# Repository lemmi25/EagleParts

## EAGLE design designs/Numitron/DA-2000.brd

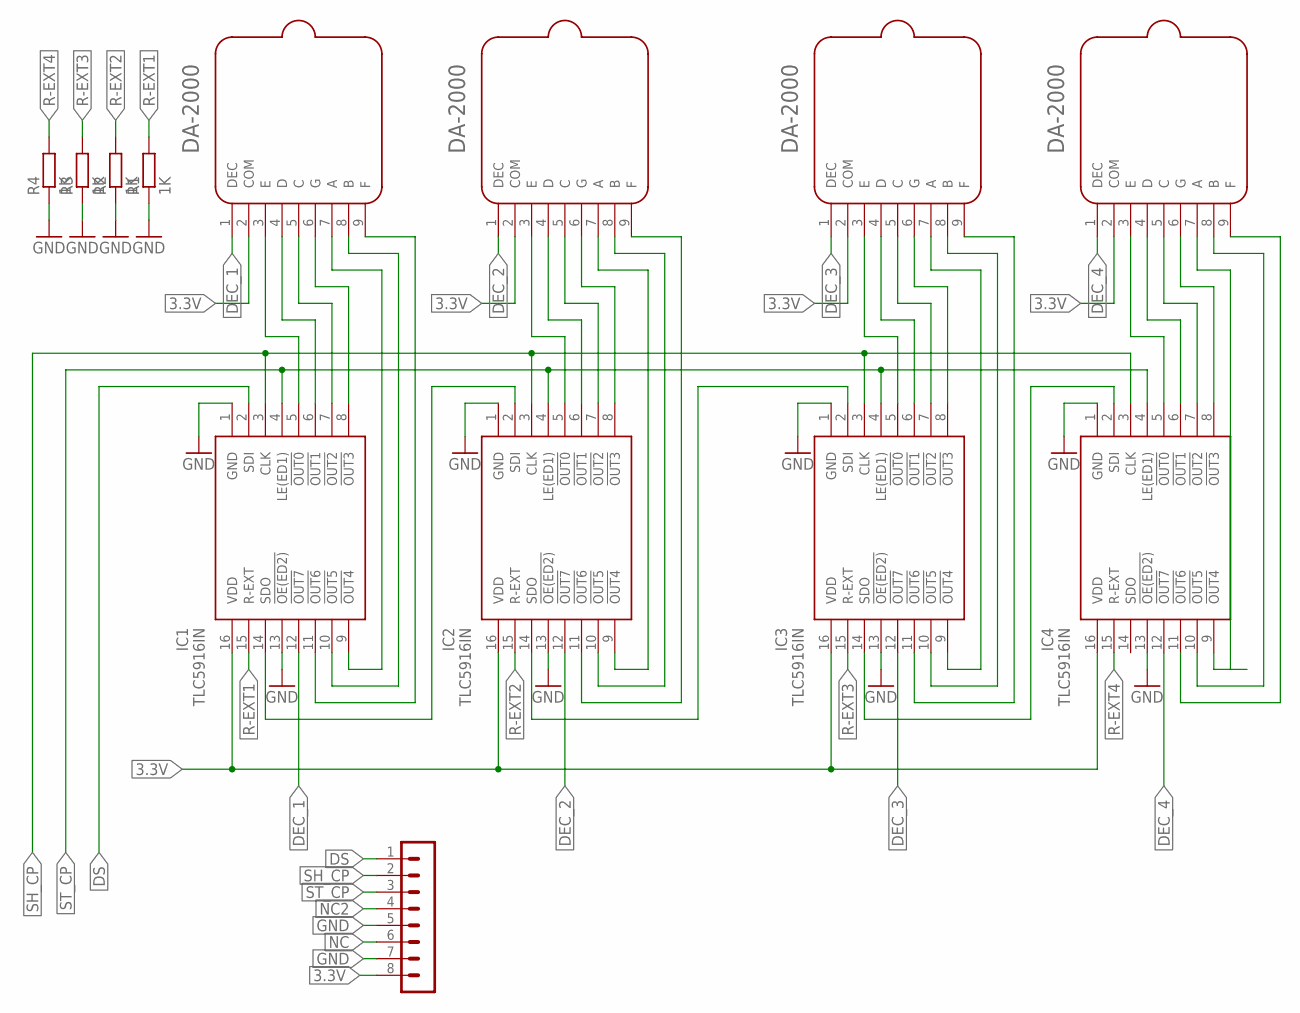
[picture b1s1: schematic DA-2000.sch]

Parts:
IC1, IC2, IC3, IC4: TLC5916IN; DIP794W53P254L1930H508Q16N
R1, R2, R3, R4: 1K; R1206
SV2: PINHEADER-1X8; MA08-1
U$1, U$2, U$3, U$4: DA-2000

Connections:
3.3V: IC1.16 (VDD), IC2.16 (VDD), IC3.16 (VDD), IC4.16 (VDD), SV2.8, U$1.2 (COM), U$2.2 (COM), U$3.2 (COM), U$4.2 (COM)
DEC_1: IC1.12 (!OUT7), U$1.1 (DEC)
DEC_2: IC2.12 (!OUT7), U$2.1 (DEC)
DEC_3: IC3.12 (!OUT7), U$3.1 (DEC)
DEC_4: IC4.12 (!OUT7), U$4.1 (DEC)
DS: IC1.2 (SDI), SV2.1
GND: IC1.1 (GND), IC1.13 (!OE(ED2)), IC2.1 (GND), IC2.13 (!OE(ED2)), IC3.1 (GND), IC3.13 (!OE(ED2)), IC4.1 (GND), IC4.13 (!OE(ED2)), R1.1, R2.1, R3.1, R4.1, SV2.5, SV2.7
unnamed: IC3.8 (!OUT3), U$3.6 (G)
unnamed: IC3.9 (!OUT4), U$3.7 (A)
unnamed: IC1.5 (!OUT0), U$1.3 (E)
unnamed: IC1.6 (!OUT1), U$1.4 (D)
unnamed: IC1.7 (!OUT2), U$1.5 (C)
unnamed: IC1.8 (!OUT3), U$1.6 (G)
unnamed: IC4.8 (!OUT3), U$4.6 (G)
unnamed: IC1.9 (!OUT4), U$1.7 (A)
unnamed: IC4.9 (!OUT4), U$4.7 (A)
unnamed: IC1.10 (!OUT5), U$1.8 (B)
unnamed: IC1.11 (!OUT6), U$1.9 (F)
unnamed: IC2.5 (!OUT0), U$2.3 (E)
unnamed: IC2.6 (!OUT1), U$2.4 (D)
unnamed: IC2.7 (!OUT2), U$2.5 (C)
unnamed: IC2.8 (!OUT3), U$2.6 (G)
unnamed: IC2.9 (!OUT4), U$2.7 (A)
unnamed: IC2.10 (!OUT5), U$2.8 (B)
unnamed: IC2.11 (!OUT6), U$2.9 (F)
unnamed: IC3.5 (!OUT0), U$3.3 (E)
unnamed: IC3.6 (!OUT1), U$3.4 (D)
unnamed: IC3.7 (!OUT2), U$3.5 (C)
unnamed: IC4.5 (!OUT0), U$4.3 (E)
unnamed: IC4.6 (!OUT1), U$4.4 (D)
unnamed: IC3.10 (!OUT5), U$3.8 (B)
unnamed: IC3.11 (!OUT6), U$3.9 (F)
unnamed: IC4.7 (!OUT2), U$4.5 (C)
unnamed: IC1.14 (SDO), IC2.2 (SDI)
unnamed: IC4.10 (!OUT5), U$4.8 (B)
unnamed: IC4.11 (!OUT6), U$4.9 (F)
unnamed: IC2.14 (SDO), IC3.2 (SDI)
unnamed: IC3.14 (SDO), IC4.2 (SDI)
NC: SV2.6
NC2: SV2.4
R-EXT1: IC1.15 (R-EXT), R1.2
R-EXT2: IC2.15 (R-EXT), R2.2
R-EXT3: IC3.15 (R-EXT), R3.2
R-EXT4: IC4.15 (R-EXT), R4.2
SH_CP: IC1.3 (CLK), IC2.3 (CLK), IC3.3 (CLK), IC4.3 (CLK), SV2.2
ST_CP: IC1.4 (LE(ED1)), IC2.4 (LE(ED1)), IC3.4 (LE(ED1)), IC4.4 (LE(ED1)), SV2.3

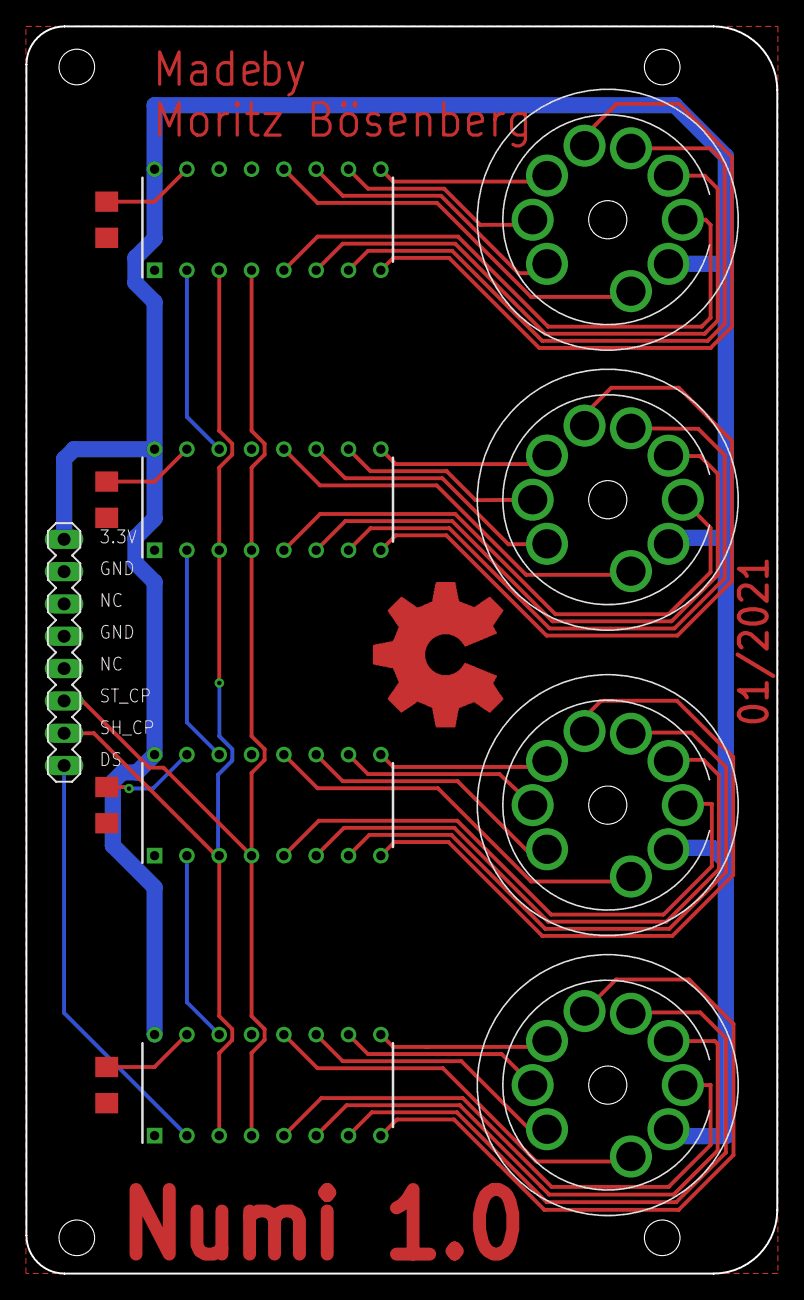
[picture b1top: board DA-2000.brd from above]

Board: 2 copper layers, 59.0 x 98.0 mm, 13 parts (0 on the bottom side), 44 nets.

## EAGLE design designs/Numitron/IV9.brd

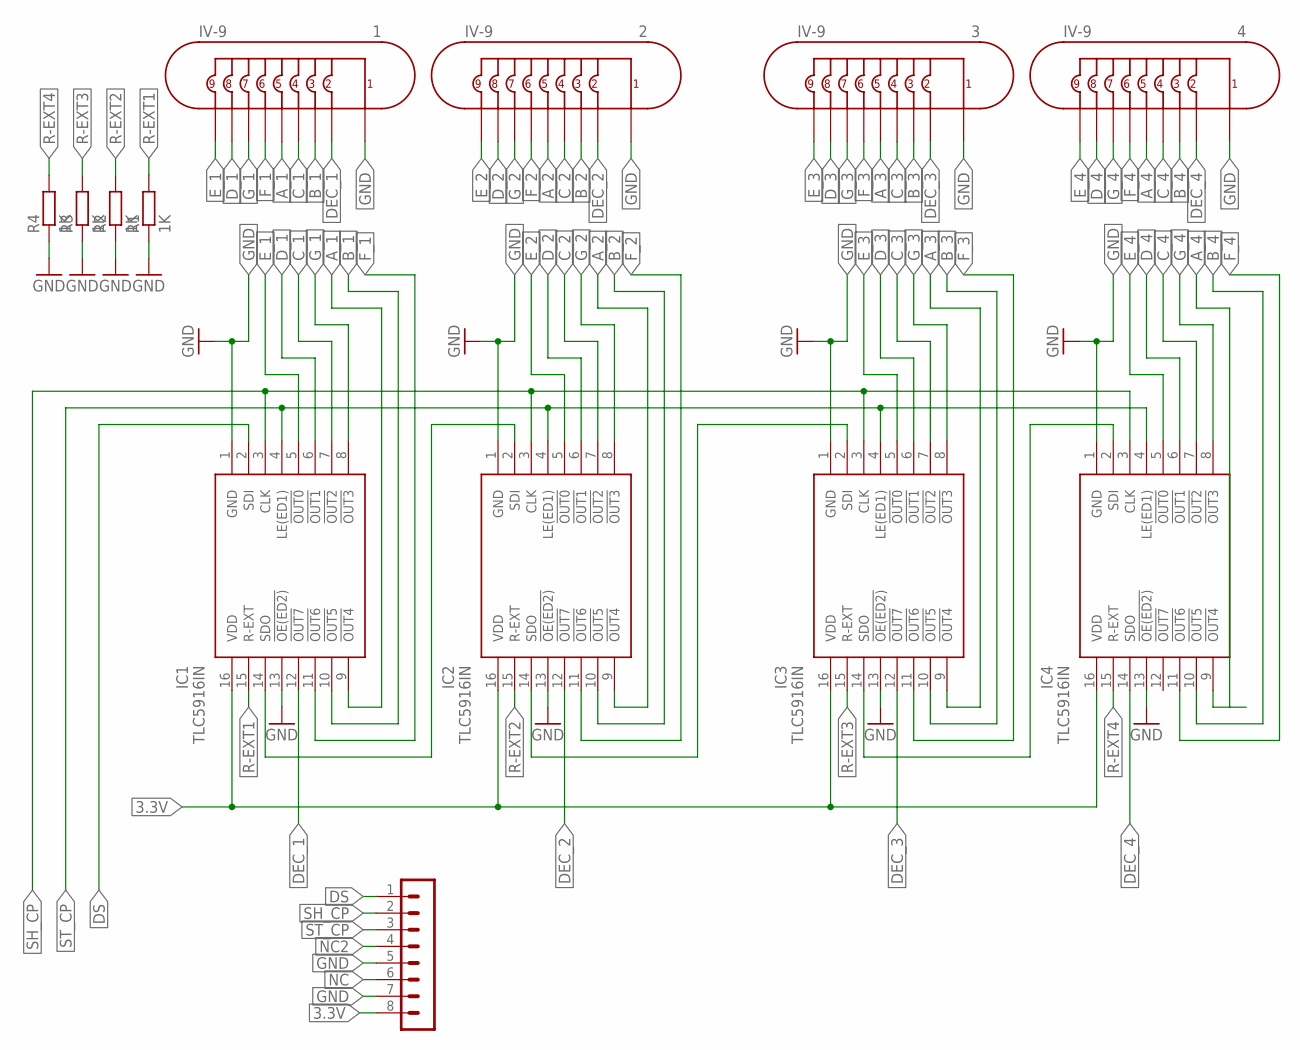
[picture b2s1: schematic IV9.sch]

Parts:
1, 2, 3, 4: IV-9
IC1, IC2, IC3, IC4: TLC5916IN; DIP794W53P254L1930H508Q16N
R1, R2, R3, R4: 1K; R1206
SV2: PINHEADER-1X8; MA08-1

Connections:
3.3V: IC1.16 (VDD), IC2.16 (VDD), IC3.16 (VDD), IC4.16 (VDD), SV2.8
A_1: 1.5, IC1.9 (!OUT4)
A_2: 2.5, IC2.9 (!OUT4)
A_3: 3.5, IC3.9 (!OUT4)
A_4: 4.5, IC4.9 (!OUT4)
B_1: 1.3, IC1.10 (!OUT5)
B_2: 2.3, IC2.10 (!OUT5)
B_3: 3.3, IC3.10 (!OUT5)
B_4: 4.3, IC4.10 (!OUT5)
C_1: 1.4, IC1.7 (!OUT2)
C_2: 2.4, IC2.7 (!OUT2)
C_3: 3.4, IC3.7 (!OUT2)
C_4: 4.4, IC4.7 (!OUT2)
DEC_1: 1.2, IC1.12 (!OUT7)
DEC_2: 2.2, IC2.12 (!OUT7)
DEC_3: 3.2, IC3.12 (!OUT7)
DEC_4: 4.2, IC4.14 (SDO)
DS: IC1.2 (SDI), SV2.1
D_1: 1.8, IC1.6 (!OUT1)
D_2: 2.8, IC2.6 (!OUT1)
D_3: 3.8, IC3.6 (!OUT1)
D_4: 4.8, IC4.6 (!OUT1)
E_1: 1.9, IC1.5 (!OUT0)
E_2: 2.9, IC2.5 (!OUT0)
E_3: 3.9, IC3.5 (!OUT0)
E_4: 4.9, IC4.5 (!OUT0)
F_1: 1.6, IC1.11 (!OUT6)
F_2: 2.6, IC2.11 (!OUT6)
F_3: 3.6, IC3.11 (!OUT6)
F_4: 4.6, IC4.11 (!OUT6)
GND: 1.1, 2.1, 3.1, 4.1, IC1.1 (GND), IC1.13 (!OE(ED2)), IC2.1 (GND), IC2.13 (!OE(ED2)), IC3.1 (GND), IC3.13 (!OE(ED2)), IC4.1 (GND), IC4.13 (!OE(ED2)), R1.1, R2.1, R3.1, R4.1, SV2.5, SV2.7
G_1: 1.7, IC1.8 (!OUT3)
G_2: 2.7, IC2.8 (!OUT3)
G_3: 3.7, IC3.8 (!OUT3)
G_4: 4.7, IC4.8 (!OUT3)
unnamed: IC1.14 (SDO), IC2.2 (SDI)
unnamed: IC2.14 (SDO), IC3.2 (SDI)
unnamed: IC3.14 (SDO), IC4.2 (SDI)
NC: SV2.6
NC2: SV2.4
R-EXT1: IC1.15 (R-EXT), R1.2
R-EXT2: IC2.15 (R-EXT), R2.2
R-EXT3: IC3.15 (R-EXT), R3.2
R-EXT4: IC4.15 (R-EXT), R4.2
SH_CP: IC1.3 (CLK), IC2.3 (CLK), IC3.3 (CLK), IC4.3 (CLK), SV2.2
ST_CP: IC1.4 (LE(ED1)), IC2.4 (LE(ED1)), IC3.4 (LE(ED1)), IC4.4 (LE(ED1)), SV2.3

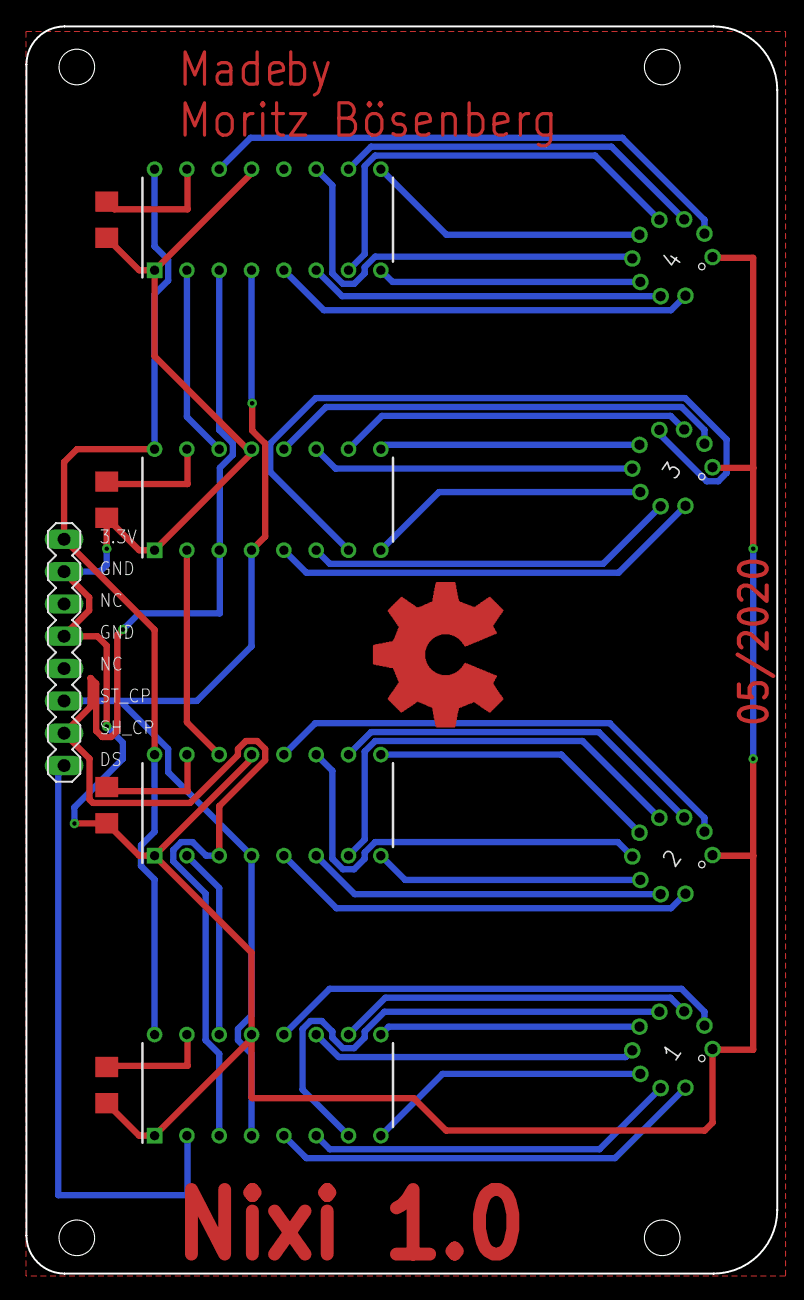
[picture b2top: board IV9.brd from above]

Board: 2 copper layers, 59.0 x 98.0 mm, 13 parts (0 on the bottom side), 44 nets.

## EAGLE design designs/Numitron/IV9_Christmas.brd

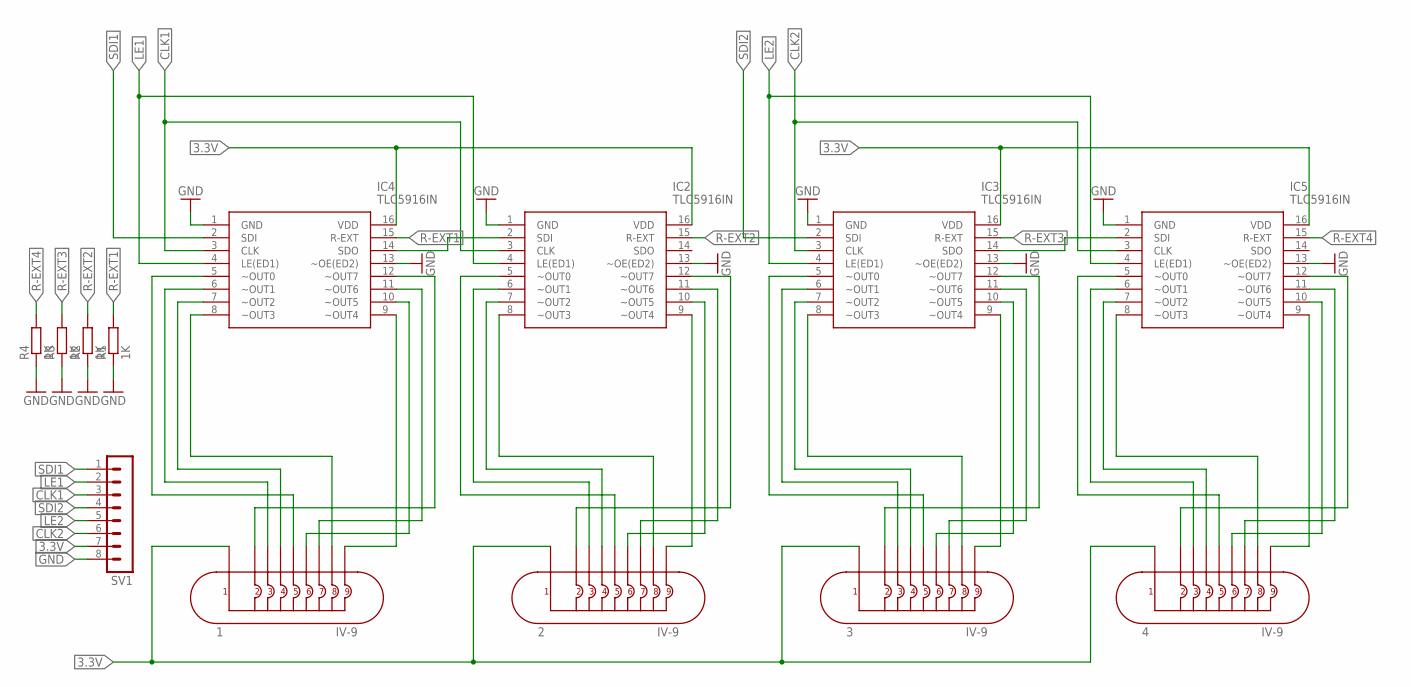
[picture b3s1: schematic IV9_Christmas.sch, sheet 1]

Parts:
1, 2, 3, 4: IV-9
IC2, IC3, IC4, IC5: TLC5916IN; DIP254P762X508-16
R1, R2, R3, R4: 1K; R1206
SV1: MA08-1

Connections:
3.3V: 1.1, 2.1, 3.1, 4.1, IC2.16 (VDD), IC3.16 (VDD), IC4.16 (VDD), IC5.16 (VDD), SV1.7
CLK1: IC2.3 (CLK), IC4.3 (CLK), SV1.3
CLK2: IC3.3 (CLK), IC5.3 (CLK), SV1.6
GND: IC2.1 (GND), IC2.13 (~OE(ED2)), IC3.1 (GND), IC3.13 (~OE(ED2)), IC4.1 (GND), IC4.13 (~OE(ED2)), IC5.1 (GND), IC5.13 (~OE(ED2)), R1.1, R2.1, R3.1, R4.1, SV1.8
LE1: IC2.4 (LE(ED1)), IC4.4 (LE(ED1)), SV1.2
LE2: IC3.4 (LE(ED1)), IC5.4 (LE(ED1)), SV1.5
unnamed: IC3.14 (SDO), IC5.2 (SDI)
unnamed: IC2.2 (SDI), IC4.14 (SDO)
unnamed: 2.8, IC2.8 (~OUT3)
unnamed: 1.5, IC4.5 (~OUT0)
unnamed: 1.3, IC4.6 (~OUT1)
unnamed: 1.4, IC4.7 (~OUT2)
unnamed: 1.8, IC4.8 (~OUT3)
unnamed: 1.9, IC4.9 (~OUT4)
unnamed: 1.6, IC4.10 (~OUT5)
unnamed: 1.7, IC4.11 (~OUT6)
unnamed: 3.5, IC3.5 (~OUT0)
unnamed: 3.3, IC3.6 (~OUT1)
unnamed: 3.4, IC3.7 (~OUT2)
unnamed: 3.6, IC3.10 (~OUT5)
unnamed: 3.7, IC3.11 (~OUT6)
unnamed: 3.2, IC3.12 (~OUT7)
unnamed: 4.5, IC5.5 (~OUT0)
unnamed: 4.3, IC5.6 (~OUT1)
unnamed: 2.9, IC2.9 (~OUT4)
unnamed: 3.8, IC3.8 (~OUT3)
unnamed: 3.9, IC3.9 (~OUT4)
unnamed: 4.8, IC5.8 (~OUT3)
unnamed: 4.9, IC5.9 (~OUT4)
unnamed: 1.2, IC4.12 (~OUT7)
unnamed: 2.5, IC2.5 (~OUT0)
unnamed: 2.3, IC2.6 (~OUT1)
unnamed: 2.4, IC2.7 (~OUT2)
unnamed: 2.6, IC2.10 (~OUT5)
unnamed: 2.7, IC2.11 (~OUT6)
unnamed: 2.2, IC2.12 (~OUT7)
unnamed: 4.4, IC5.7 (~OUT2)
unnamed: 4.6, IC5.10 (~OUT5)
unnamed: 4.7, IC5.11 (~OUT6)
unnamed: 4.2, IC5.12 (~OUT7)
R-EXT1: IC4.15 (R-EXT), R1.2
R-EXT2: IC2.15 (R-EXT), R2.2
R-EXT3: IC3.15 (R-EXT), R3.2
R-EXT4: IC5.15 (R-EXT), R4.2
SDI1: IC4.2 (SDI), SV1.1
SDI2: IC3.2 (SDI), SV1.4

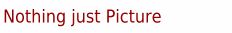
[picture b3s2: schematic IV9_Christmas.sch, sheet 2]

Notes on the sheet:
Nothing just Picture

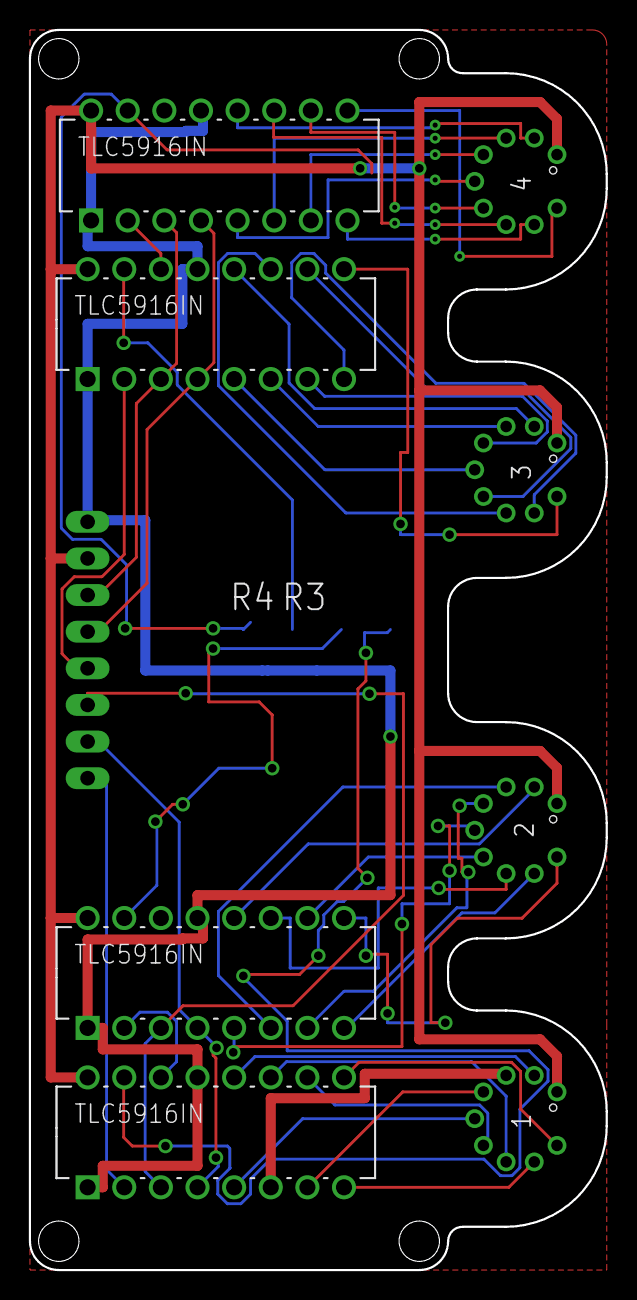
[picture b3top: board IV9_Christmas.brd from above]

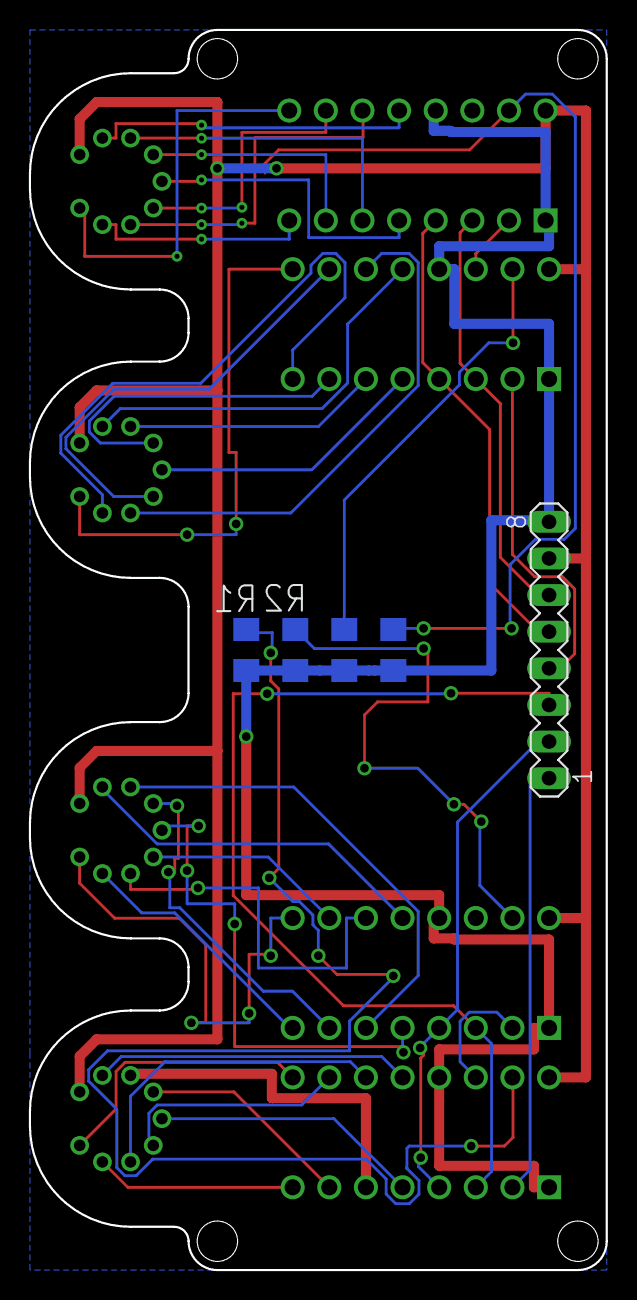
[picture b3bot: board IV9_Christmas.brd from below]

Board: 2 copper layers, 40.0 x 86.0 mm, 13 parts (5 on the bottom side), 46 nets.

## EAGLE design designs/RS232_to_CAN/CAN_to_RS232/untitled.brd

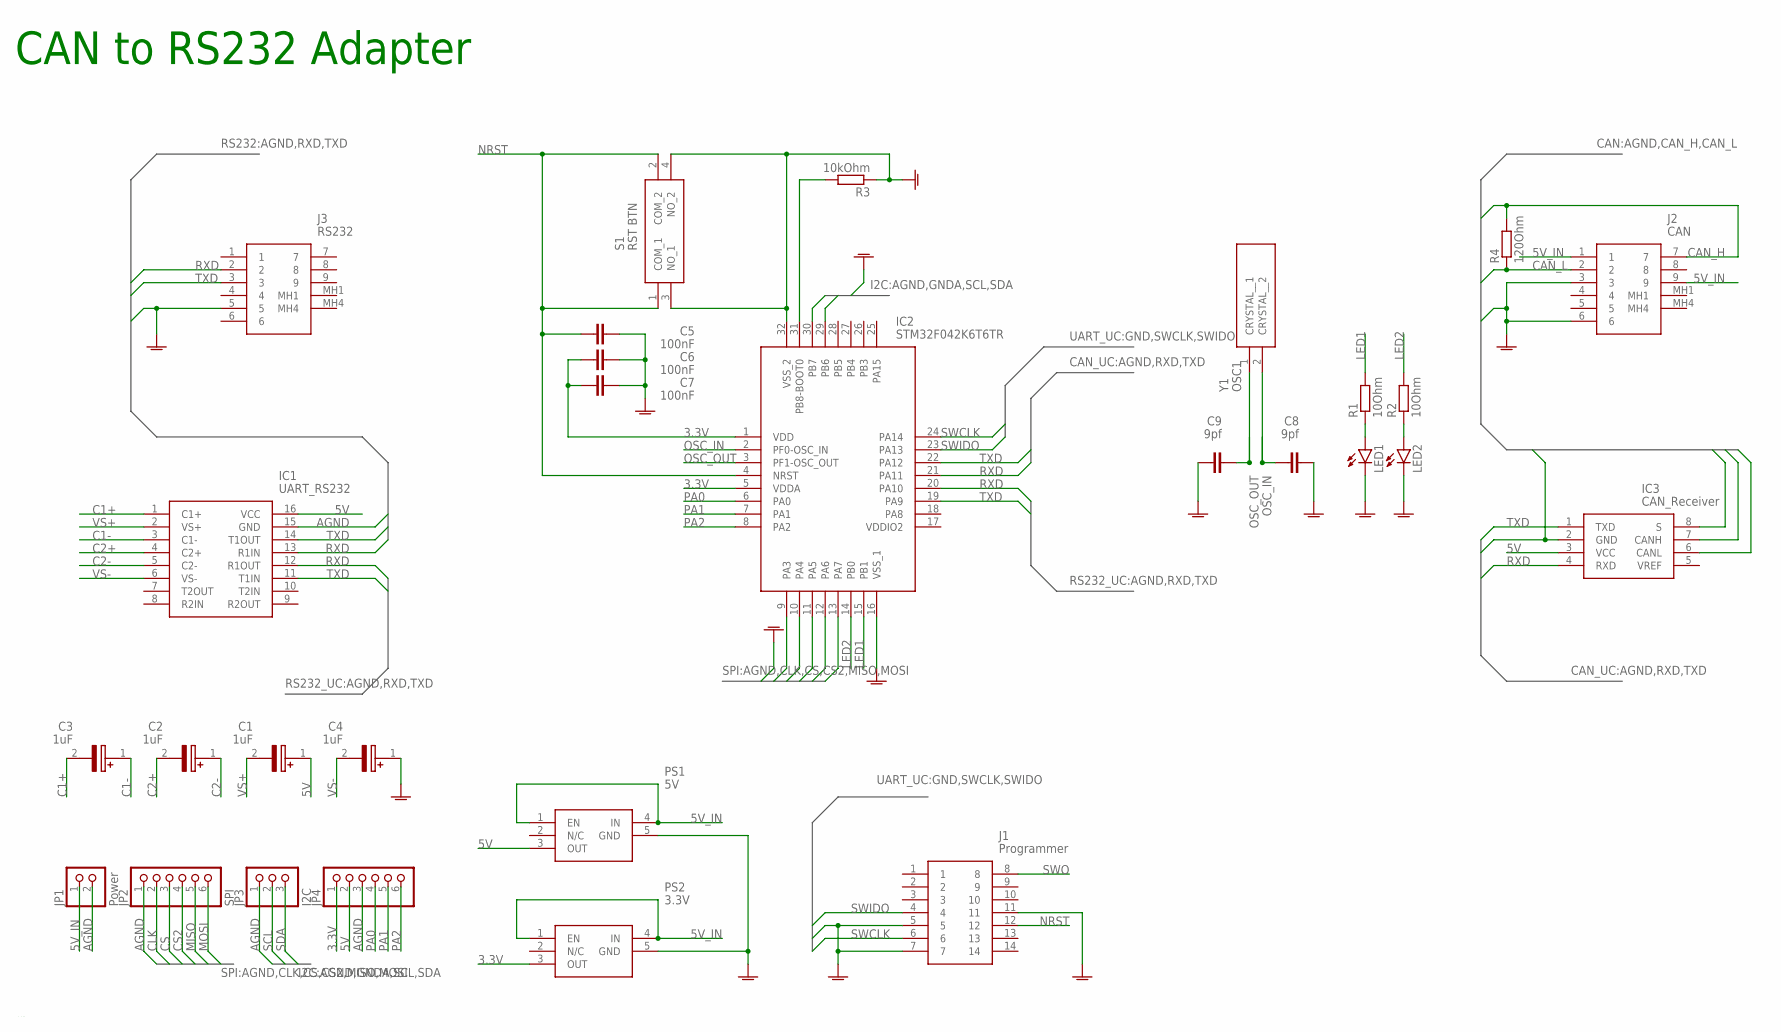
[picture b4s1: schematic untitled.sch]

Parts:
C1, C2, C3, C4: 1uF; CAPAE430X550N
C5, C6, C7: 100nF; C0805
C8, C9: 9pf; C0805
IC1: UART_RS232; SOIC127P600X175-16N
IC2: STM32F042K6T6TR; QFP80P900X900X160-32N
IC3: CAN_Receiver; SOIC127P600X175-8N
J1: Programmer; FTSH10701LDVKA
J2: CAN; K202XHTE9SN
J3: RS232; K202XHTE9SN
JP1: Power; 1X02/90
JP2: SPI; 1X06/90
JP3: I2C; 1X03/90
JP4: PINHD-1X6/90; 1X06/90
LED1, LED2: LED_805SML0805; SML0805
PS1: 5V; SOT150P700X160-5N
PS2: 3.3V; SOT150P700X160-5N
R1, R2: 10Ohm; R0805
R3: 10kOhm; R0805
R4: 120Ohm; R0805
S1: RST BTN; PTS526SM15SMTR2LFS
Y1: OSC1; CM7VT1A32768KHZ7PF100PPMTAQC

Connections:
3.3V: C6.1, C7.1, IC2.1 (VDD), IC2.5 (VDDA), JP4.1, PS2.3 (OUT)
5V: C1.1 (+), IC1.16 (VCC), IC3.3 (VCC), JP4.2, PS1.3 (OUT)
5V_IN: J2.1, J2.9, JP1.1, PS1.1 (EN), PS1.4 (IN), PS2.1 (EN), PS2.4 (IN)
AGND: IC1.15 (GND), IC3.2 (GND), IC3.8 (S), J2.3, J2.6, J3.5, JP1.2, JP2.1, JP3.1, JP4.3
C1+: C3.2 (-), IC1.1 (C1+)
C1-: C3.1 (+), IC1.3 (C1-)
C2+: C2.2 (-), IC1.4 (C2+)
C2-: C2.1 (+), IC1.5 (C2-)
CAN_H: IC3.7 (CANH), J2.7, R4.2
CAN_L: IC3.6 (CANL), J2.2, R4.1
CLK: IC2.11 (PA5), JP2.2
CS: IC2.10 (PA4), JP2.3
CS2: IC2.9 (PA3), JP2.4
GND: J1.5, J1.7
GNDA: C4.1 (+), C5.2, C6.2, C7.2, C8.2, C9.1, IC2.16 (VSS_1), IC2.32 (VSS_2), J1.11, LED1.C, LED2.C, PS1.5 (GND), PS2.5 (GND), R3.1, S1.3 (NO_1), S1.4 (NO_2)
LED1: IC2.15 (PB1), R1.2
LED2: IC2.14 (PB0), R2.2
MISO: IC2.12 (PA6), JP2.5
MOSI: IC2.13 (PA7), JP2.6
unnamed: LED1.A, R1.1
unnamed: LED2.A, R2.1
unnamed: IC2.31 (PB8-BOOT0), R3.2
NRST: C5.1, IC2.4 (NRST), J1.12, S1.1 (COM_1), S1.2 (COM_2)
OSC_IN: C8.1, IC2.2 (PF0-OSC_IN), Y1.2 (CRYSTAL__2)
OSC_OUT: C9.2, IC2.3 (PF1-OSC_OUT), Y1.1 (CRYSTAL__1)
PA0: IC2.6 (PA0), JP4.4
PA1: IC2.7 (PA1), JP4.5
PA2: IC2.8 (PA2), JP4.6
RXD: IC1.12 (R1OUT), IC1.13 (R1IN), IC2.20 (PA10), IC2.21 (PA11), IC3.4 (RXD), J3.2
SCL: IC2.29 (PB6), JP3.2
SDA: IC2.30 (PB7), JP3.3
SWCLK: IC2.24 (PA14), J1.6
SWIDO: IC2.23 (PA13), J1.4
SWO: J1.8
TXD: IC1.11 (T1IN), IC1.14 (T1OUT), IC2.19 (PA9), IC2.22 (PA12), IC3.1 (TXD), J3.3
VS+: C1.2 (-), IC1.2 (VS+)
VS-: C4.2 (-), IC1.6 (VS-)

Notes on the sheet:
CAN to RS232 Adapter
/Users/moritzbosenberg/Desktop/GIT/EagleParts/designs/OpenHardware.bmp

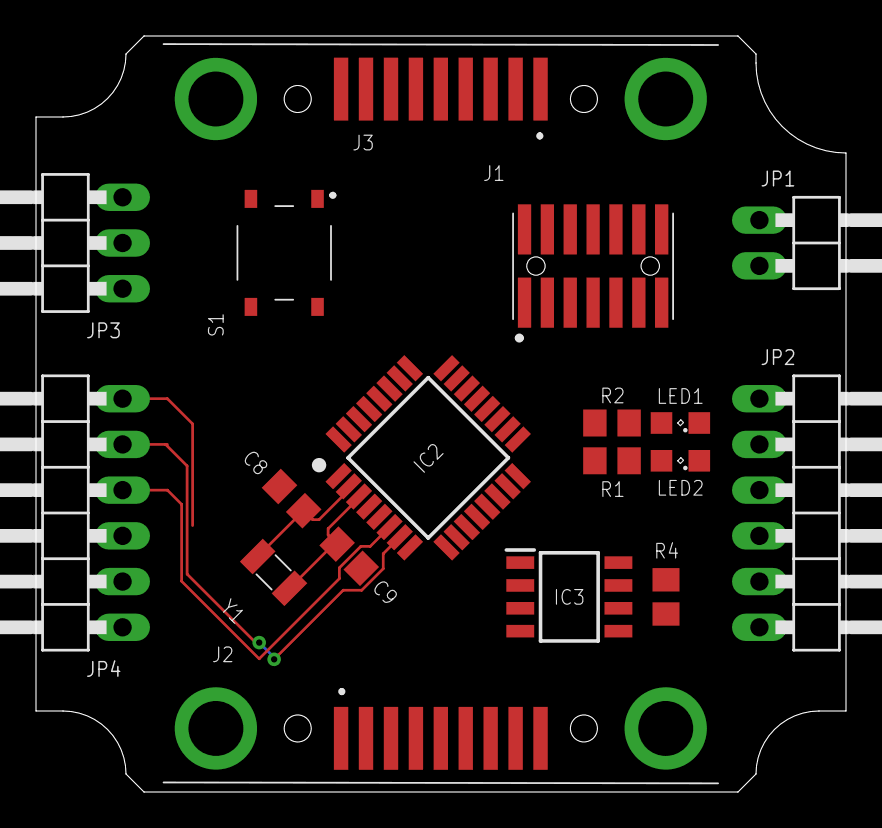
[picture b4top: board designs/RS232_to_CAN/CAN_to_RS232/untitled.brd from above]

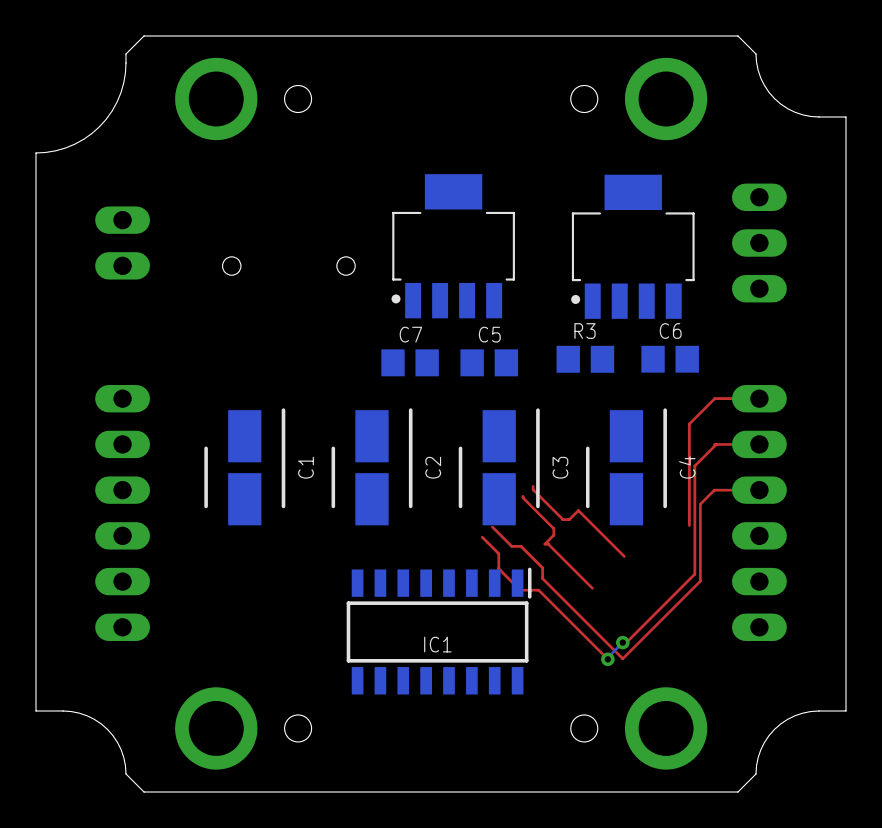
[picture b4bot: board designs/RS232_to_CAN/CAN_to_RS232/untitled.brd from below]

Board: 2 copper layers, 45.0 x 42.0 mm, 29 parts (11 on the bottom side), 36 nets.

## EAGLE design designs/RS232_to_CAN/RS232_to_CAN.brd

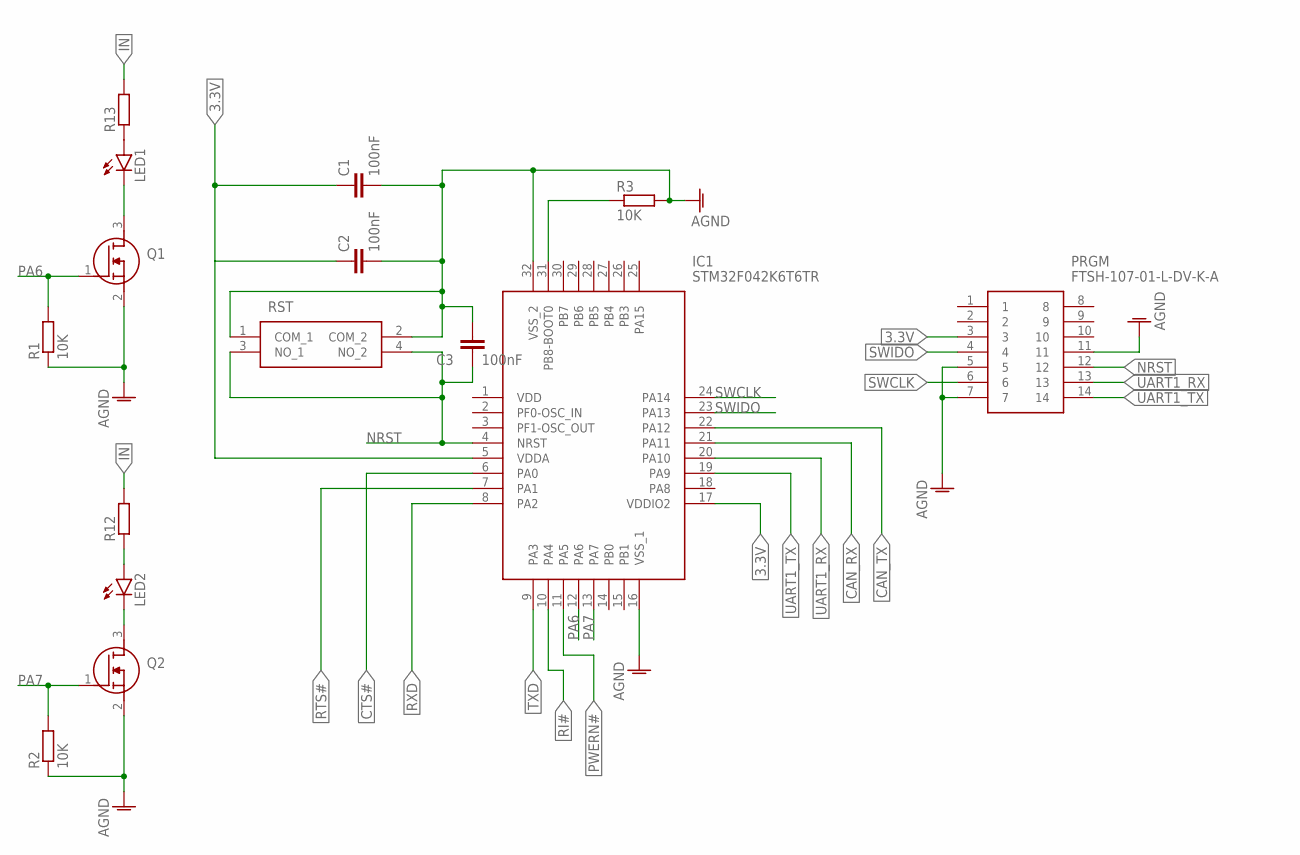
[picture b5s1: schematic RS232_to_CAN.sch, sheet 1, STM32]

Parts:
C1, C2, C3: 100nF; C0805
IC1: STM32F042K6T6TR; QFP80P900X900X160-32N
LED1, LED2: LED_1206SMT1206; 1206
PRGM: FTSH-107-01-L-DV-K-A; FTSH10701LDVKA
Q1, Q2: FDN5632N-F085; SOT95P237X122-3N
R1, R2: 10K; R0805
R3: 10K; R1206
R12, R13: R-EU_805R0805; R0805
RST: PTS526_SM15_SMTR2_LFS; PTS526SM15SMTR2LFS

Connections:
3.3V: C1.1, C2.1, IC1.5 (VDDA), IC1.17 (VDDIO2), PRGM.3; also elsewhere on the board
AGND: C1.2, C2.2, C3.1, IC1.16 (VSS_1), IC1.32 (VSS_2), PRGM.5, PRGM.7, PRGM.11, Q1.2 (S), Q2.2 (S), R1.1, R2.1, R3.2, RST.1 (COM_1), RST.2 (COM_2); also elsewhere on the board
CAN_RX: IC1.21 (PA11); also elsewhere on the board
CAN_TX: IC1.22 (PA12); also elsewhere on the board
CTS#: IC1.6 (PA0); also elsewhere on the board
IN: LED1.C, LED2.C, Q1.3 (D), Q2.3 (D); also elsewhere on the board
unnamed: LED1.A, R13.1
unnamed: IC1.31 (PB8-BOOT0), R3.1
unnamed: LED2.A, R12.1
NRST: C3.2, IC1.4 (NRST), PRGM.12, RST.3 (NO_1), RST.4 (NO_2)
PA6: IC1.12 (PA6), Q1.1 (G), R1.2
PA7: IC1.13 (PA7), Q2.1 (G), R2.2
PWERN#: IC1.11 (PA5); also elsewhere on the board
RI#: IC1.10 (PA4); also elsewhere on the board
RTS#: IC1.7 (PA1); also elsewhere on the board
RXD: IC1.8 (PA2); also elsewhere on the board
SWCLK: IC1.24 (PA14), PRGM.6
SWIDO: IC1.23 (PA13), PRGM.4
TXD: IC1.9 (PA3); also elsewhere on the board
UART1_RX: IC1.20 (PA10), PRGM.13; also elsewhere on the board
UART1_TX: IC1.19 (PA9), PRGM.14; also elsewhere on the board

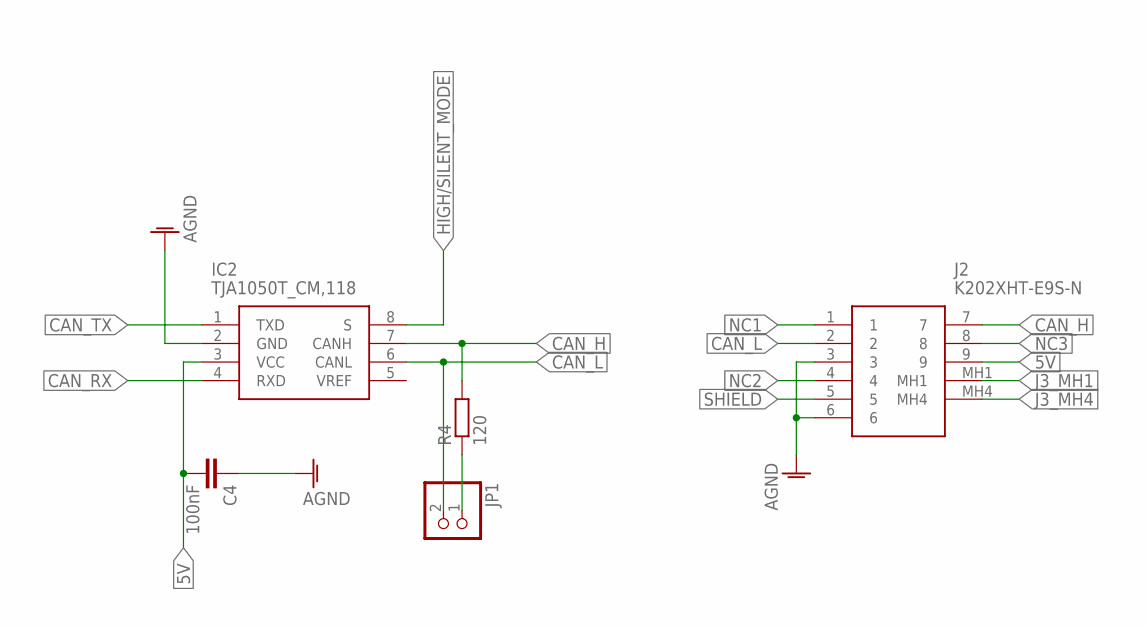
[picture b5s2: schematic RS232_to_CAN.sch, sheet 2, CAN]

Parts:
C4: 100nF; C1206
IC2: TJA1050T_CM,118; SOIC127P600X175-8N
J2: K202XHT-E9S-N; K202XHTE9SN
JP1: PINHEADER-1X2; 1X02
R4: 120; R1206

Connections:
5V: C4.2, IC2.3 (VCC), J2.9; also elsewhere on the board
AGND: C4.1, IC2.2 (GND), J2.3, J2.6; also elsewhere on the board
CAN_H: IC2.7 (CANH), J2.7, R4.2
CAN_L: IC2.6 (CANL), J2.2, JP1.2
CAN_RX: IC2.4 (RXD); also elsewhere on the board
CAN_TX: IC2.1 (TXD); also elsewhere on the board
HIGH/SILENT_MODE: IC2.8 (S)
J3_MH1: J2.MH1
J3_MH4: J2.MH4
unnamed: JP1.1, R4.1
NC1: J2.1
NC2: J2.4
NC3: J2.8
SHIELD: J2.5; also elsewhere on the board

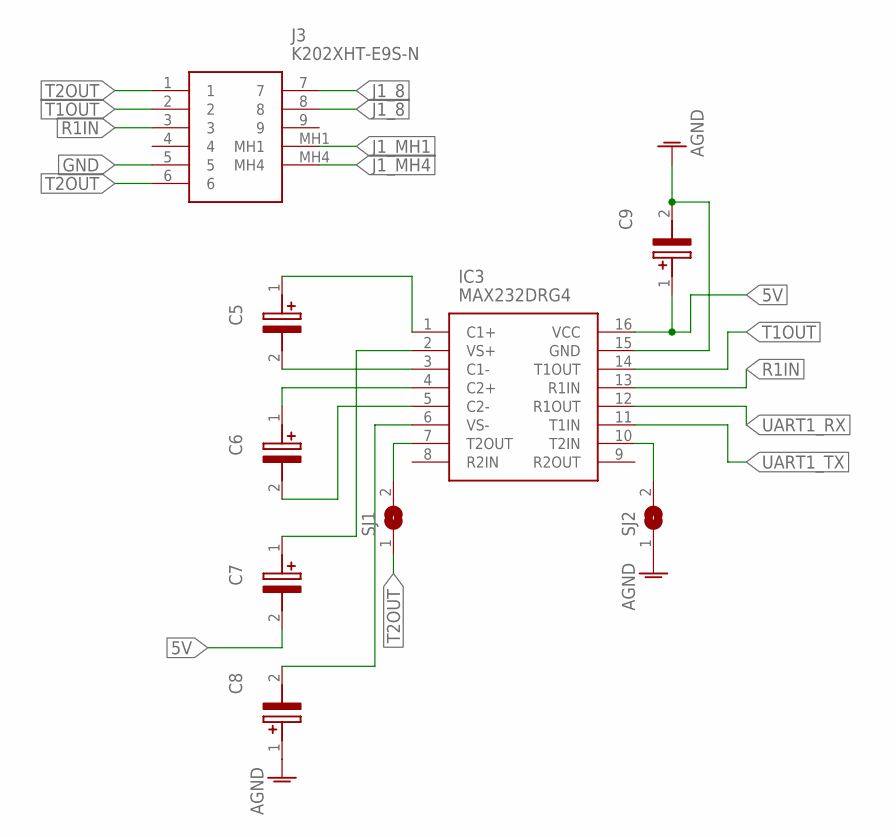
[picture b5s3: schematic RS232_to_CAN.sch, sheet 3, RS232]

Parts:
C5, C6, C7, C8, C9: UWX1H010MCL2GB; CAPAE430X550N
IC3: MAX232DRG4; SOIC127P600X175-16N
J3: K202XHT-E9S-N; K202XHTE9SN
SJ1, SJ2: SJ

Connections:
5V: C7.2 (-), C9.1 (+), IC3.16 (VCC); also elsewhere on the board
AGND: C8.1 (+), C9.2 (-), IC3.15 (GND), SJ2.1; also elsewhere on the board
GND: J3.5
J1_8: J3.7, J3.8
J1_MH1: J3.MH1
J1_MH4: J3.MH4
unnamed: C5.1 (+), IC3.1 (C1+)
unnamed: C5.2 (-), IC3.3 (C1-)
unnamed: C6.1 (+), IC3.4 (C2+)
unnamed: C6.2 (-), IC3.5 (C2-)
unnamed: C7.1 (+), IC3.2 (VS+)
unnamed: C8.2 (-), IC3.6 (VS-)
unnamed: IC3.10 (T2IN), SJ2.2
R1IN: IC3.13 (R1IN), J3.3
T1OUT: IC3.14 (T1OUT), J3.2
T2OUT: IC3.7 (T2OUT), J3.1, J3.6, SJ1.1, SJ1.2
UART1_RX: IC3.12 (R1OUT); also elsewhere on the board
UART1_TX: IC3.11 (T1IN); also elsewhere on the board

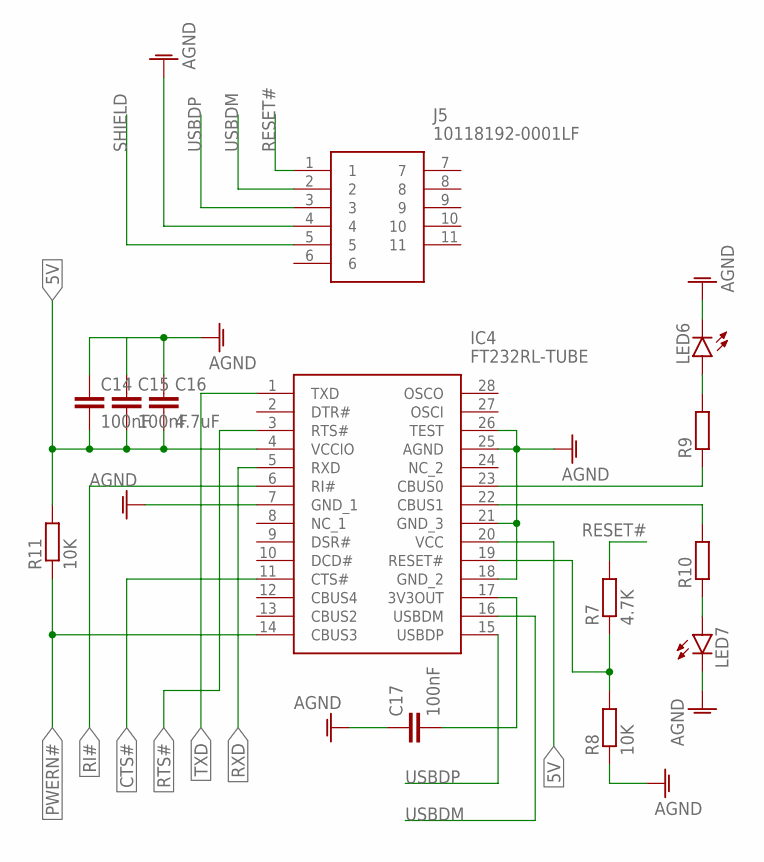
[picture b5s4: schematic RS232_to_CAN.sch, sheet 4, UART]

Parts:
C14, C15, C17: 100nF; C1206
C16: 4.7uF; C1206
IC4: FT232RL-TUBE; SOP65P780X200-28N
J5: 10118192-0001LF; 101181920001LF
LED6, LED7: LED_1206SMT1206; 1206
R7: 4.7K; R1206
R8, R11: 10K; R1206
R9, R10: R-EU_1206R1206; R1206

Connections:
5V: C14.2, C15.2, C16.2, IC4.4 (VCCIO), IC4.20 (VCC), R11.2; also elsewhere on the board
AGND: C14.1, C15.1, C16.1, C17.1, IC4.7 (GND_1), IC4.18 (GND_2), IC4.21 (GND_3), IC4.25 (AGND), IC4.26 (TEST), J5.4, LED6.C, LED7.C, R8.1; also elsewhere on the board
CTS#: IC4.11 (CTS#); also elsewhere on the board
unnamed: C17.2, IC4.17 (3V3OUT)
unnamed: IC4.19 (RESET#), R7.1, R8.2
unnamed: IC4.23 (CBUS0), R9.1
unnamed: IC4.22 (CBUS1), R10.2
unnamed: LED6.A, R9.2
unnamed: LED7.A, R10.1
PWERN#: IC4.14 (CBUS3), R11.1; also elsewhere on the board
RESET#: J5.1, R7.2
RI#: IC4.6 (RI#); also elsewhere on the board
RTS#: IC4.3 (RTS#); also elsewhere on the board
RXD: IC4.5 (RXD); also elsewhere on the board
SHIELD: J5.5; also elsewhere on the board
TXD: IC4.1 (TXD); also elsewhere on the board
USBDM: IC4.16 (USBDM), J5.2
USBDP: IC4.15 (USBDP), J5.3

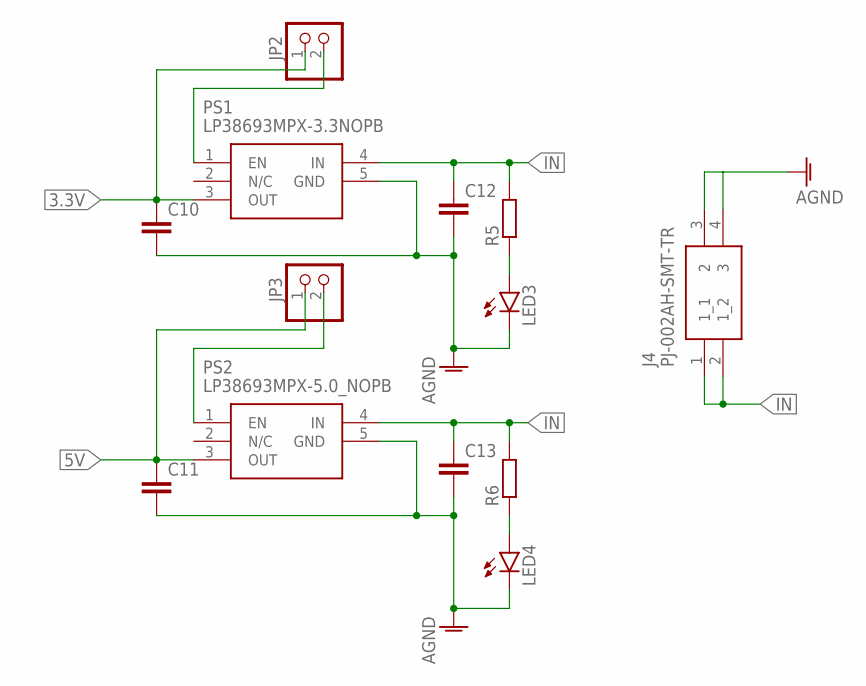
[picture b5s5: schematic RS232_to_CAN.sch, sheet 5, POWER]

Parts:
C10, C11, C12, C13: C-EU_805C0805; C0805
J4: PJ-002AH-SMT-TR
JP2, JP3: PINHEADER-1X2; 1X02
LED3, LED4: LED_1206SMT1206; 1206
PS1: LP38693MPX-3.3NOPB; SOT150P700X160-5N
PS2: LP38693MPX-5.0_NOPB; SOT150P700X160-5N
R5, R6: R-EU_1206R1206; R1206

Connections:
3.3V: C10.1, JP2.1, PS1.3 (OUT); also elsewhere on the board
5V: C11.1, JP3.1, PS2.3 (OUT); also elsewhere on the board
AGND: C10.2, C11.2, C12.2, C13.2, J4.3 (2), J4.4 (3), LED3.C, LED4.C, PS1.5 (GND), PS2.5 (GND); also elsewhere on the board
IN: C12.1, C13.1, J4.1 (1_1), J4.2 (1_2), PS1.4 (IN), PS2.4 (IN), R5.2, R6.2; also elsewhere on the board
unnamed: LED4.A, R6.1
unnamed: JP3.2, PS2.1 (EN)
unnamed: JP2.2, PS1.1 (EN)
unnamed: LED3.A, R5.1
